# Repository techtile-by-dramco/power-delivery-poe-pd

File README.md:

# Power delivery board 

This powered device (PD) board is made for the Techtile infrastructure and separates the voltage from the data coming from the ethernet CAT6 24AWG cable. It further converts the voltage to a lower usable 5V voltage with a galvanically isolated dc/dc converter (maximum output power 20W). This board is compatible with the IEEE802.3af/at/bt standard. 

To comply with the IEEE 802.3 standard a delay network was added. This prevents excessive startup power that occurs due to the high input capacitors of the DC/DC converters. During INRUSH state, the power may not exceed Power Class 3 (approximately 13W). Otherwise, the PSE may turn off the PD. (See standard and datasheet NCP1096)

Several USBs and connectors are available to power the peripherals on each tile.

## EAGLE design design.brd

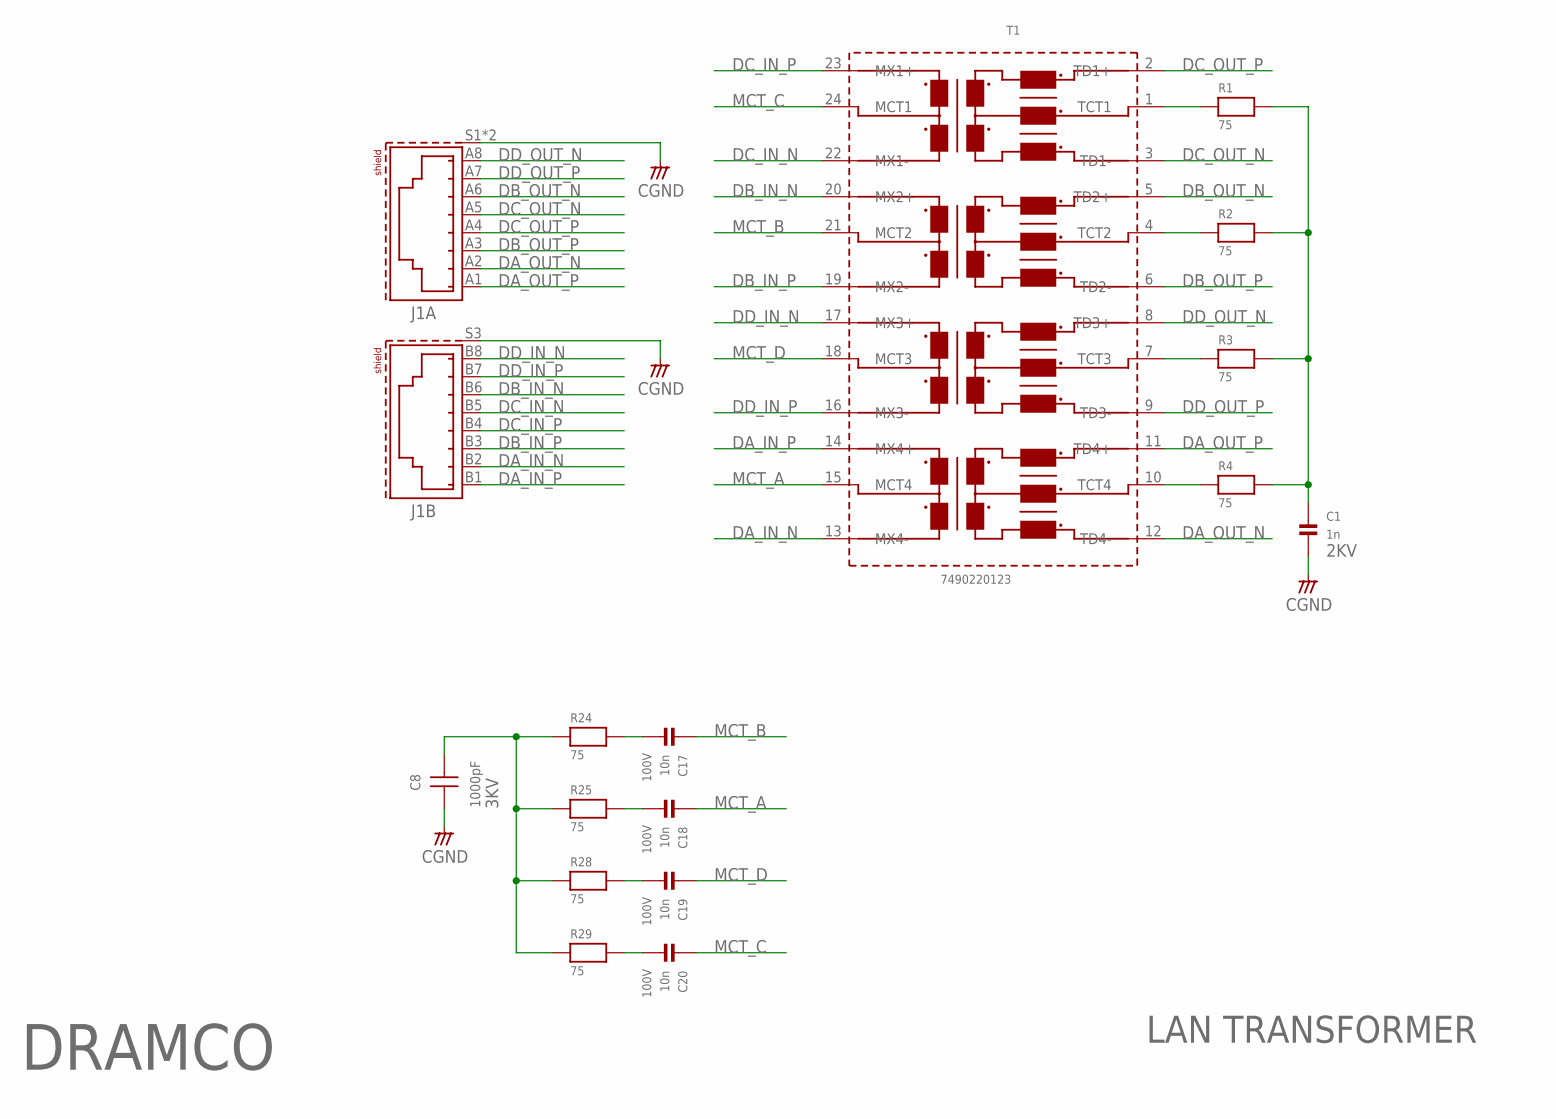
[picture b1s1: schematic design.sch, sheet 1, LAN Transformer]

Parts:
C1: 1n; 1206
C8: 1000pF; WCAP-CSMH_1808_H2.0
C17, C18, C19, C20: 10n; 0603
J1: 615016137621
R1, R2, R3, R4, R24, R25, R28, R29: 75; 0805
T1: 7490220123; 749022012X

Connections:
CGND: C1.2, C8.1, J1.S1 (SHIELD), J1.S2 (SHIELD), J1.S3 (SHIELD)
DA_IN_N: J1.B2 (7), T1.13 (MX4-)
DA_IN_P: J1.B1 (8), T1.14 (MX4+)
DA_OUT_N: J1.A2 (7), T1.12 (TD4-)
DA_OUT_P: J1.A1 (8), T1.11 (TD4+)
DB_IN_N: J1.B6 (3), T1.20 (MX2+)
DB_IN_P: J1.B3 (6), T1.19 (MX2-)
DB_OUT_N: J1.A6 (3), T1.5 (TD2+)
DB_OUT_P: J1.A3 (6), T1.6 (TD2-)
DC_IN_N: J1.B5 (4), T1.22 (MX1-)
DC_IN_P: J1.B4 (5), T1.23 (MX1+)
DC_OUT_N: J1.A5 (4), T1.3 (TD1-)
DC_OUT_P: J1.A4 (5), T1.2 (TD1+)
DD_IN_N: J1.B8 (1), T1.17 (MX3+)
DD_IN_P: J1.B7 (2), T1.16 (MX3-)
DD_OUT_N: J1.A8 (1), T1.8 (TD3+)
DD_OUT_P: J1.A7 (2), T1.9 (TD3-)
MCT_A: C18.1, T1.15 (MCT4); also elsewhere on the board
MCT_B: C17.1, T1.21 (MCT2); also elsewhere on the board
MCT_C: C20.1, T1.24 (MCT1); also elsewhere on the board
MCT_D: C19.1, T1.18 (MCT3); also elsewhere on the board
unnamed: R4.1, T1.10 (TCT4)
unnamed: R3.1, T1.7 (TCT3)
unnamed: R2.1, T1.4 (TCT2)
unnamed: R1.1, T1.1 (TCT1)
unnamed: C1.1, R1.2, R2.2, R3.2, R4.2
unnamed: C8.2, R24.1, R25.1, R28.1, R29.1
unnamed: C17.2, R24.2
unnamed: C18.2, R25.2
unnamed: C19.2, R28.2
unnamed: C20.2, R29.2

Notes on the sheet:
2KV
3KV
100V
LAN TRANSFORMER
DRAMCO

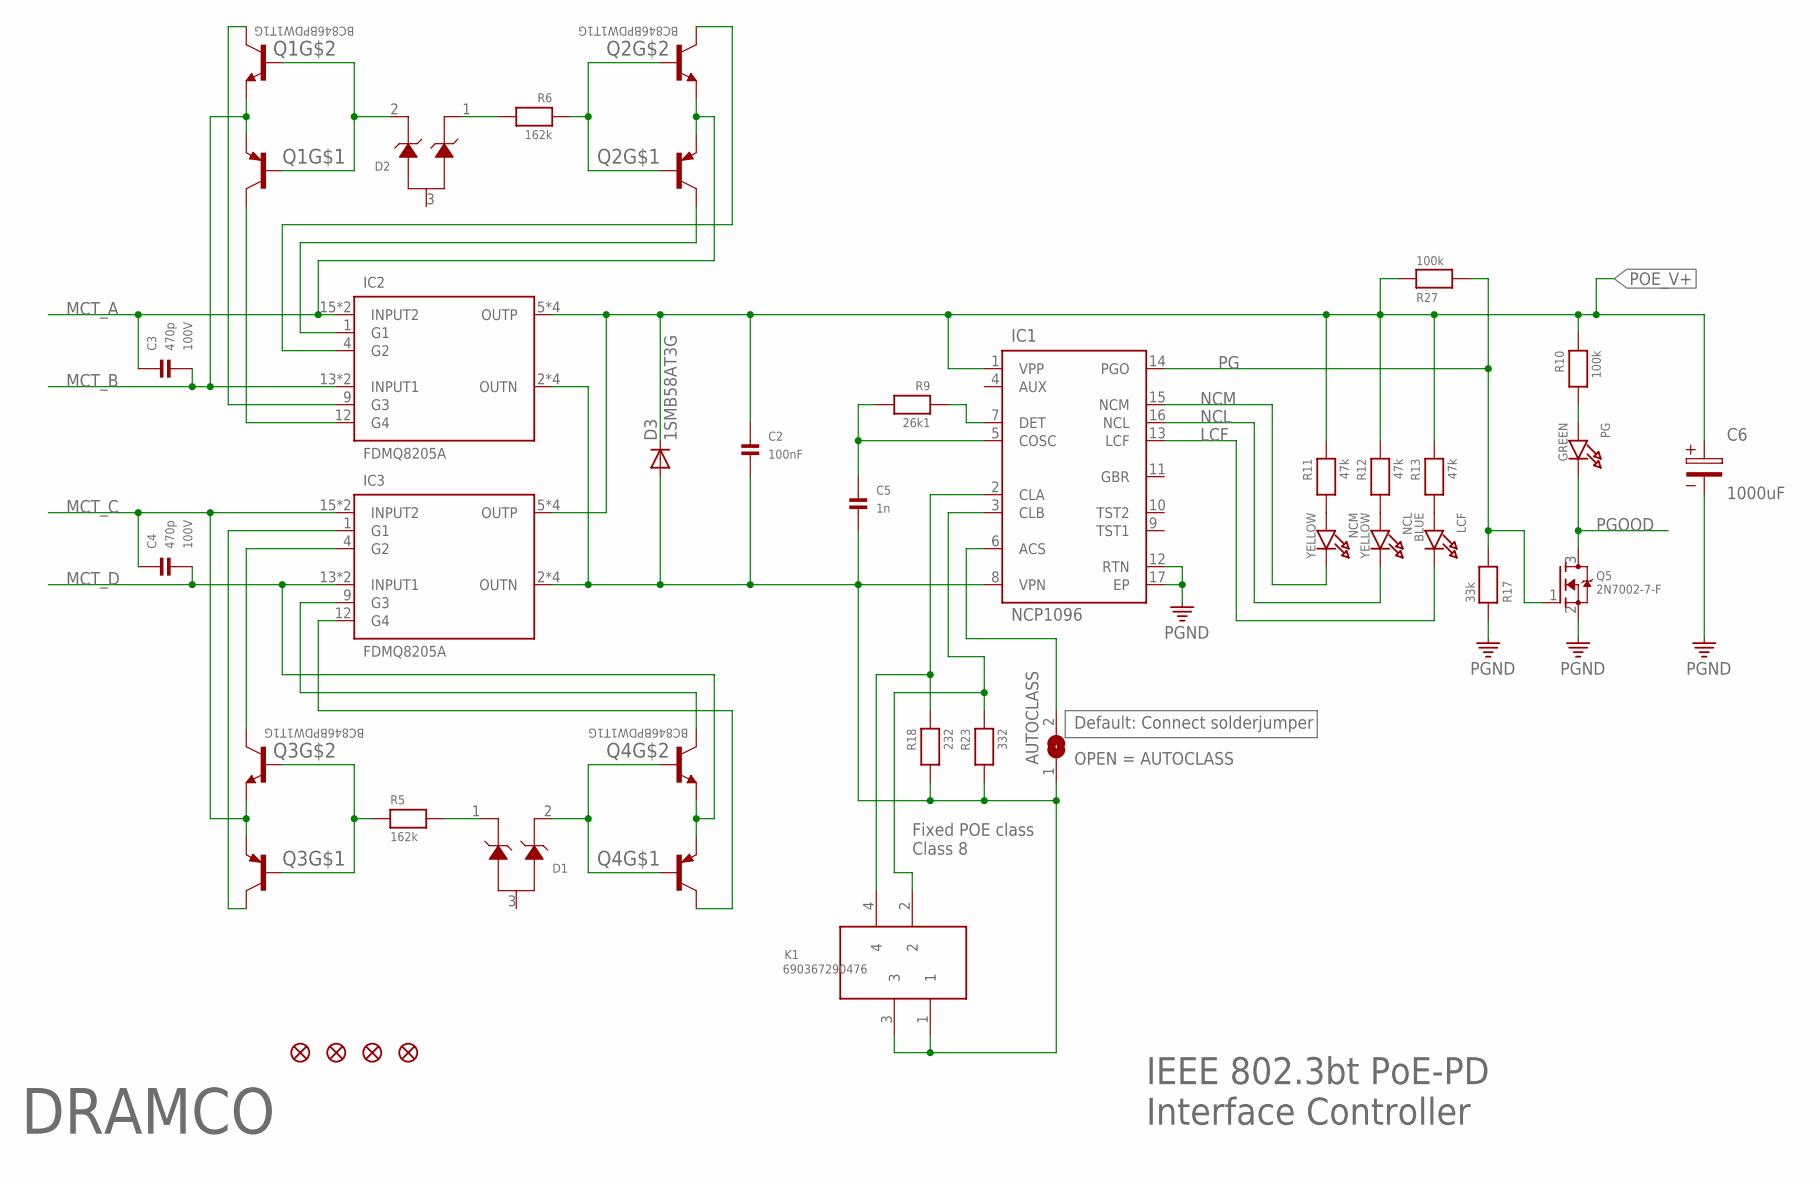
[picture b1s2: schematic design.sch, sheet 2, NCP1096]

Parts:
AUTOCLASS: SOLDERJUMPERREFLOW; SOLDERJUMPER_REFLOW
C2: 100nF; 0805
C3, C4: 470p; 0603
C5: 1n; 0603
C6: 1000uF; 16X7.5X1.1(DXAXB)
D1, D2: MMBZ27VALT1G; SOT95P237X111-3N
D3: 1SMB58AT3G; DO-214AC
FID1, FID2, FID3, FID5: FIDUCIAL""; FIDUCIAL_1MM
IC1: NCP1096; TSSOP16
IC2, IC3: FDMQ8205A; WDFN-12
K1: 690367290476
LCF: BLUE; CHIPLED_0805
NCL: YELLOW; CHIPLED_0805
NCM: YELLOW; CHIPLED_0805
PG: GREEN; CHIPLED_0805
Q1, Q2, Q3, Q4: BC846BPDW1T1G; SOT65P210X110-6N
Q5: 2N7002-7-F; SOT23-WIDE
R5, R6: 162k; 0603
R9: 26k1; 0603
R10, R27: 100k; 0603
R11, R12, R13: 47k; 0603
R17: 33k; 0603
R18: 232; 0603
R23: 332; 0603

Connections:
LCF: IC1.13 (LCF), LCF.C
MCT_A: C3.1, IC2.15 (INPUT2), IC2.16 (INPUT2), Q2.1 (E2), Q2.4 (E1); also elsewhere on the board
MCT_B: C3.2, IC2.13 (INPUT1), IC2.14 (INPUT1), Q1.1 (E2), Q1.4 (E1); also elsewhere on the board
MCT_C: C4.1, IC3.15 (INPUT2), IC3.16 (INPUT2), Q3.1 (E2), Q3.4 (E1); also elsewhere on the board
MCT_D: C4.2, IC3.13 (INPUT1), IC3.14 (INPUT1), Q4.1 (E2), Q4.4 (E1); also elsewhere on the board
unnamed: IC1.2 (CLA), K1.4, R18.1
unnamed: NCM.A, R11.2
unnamed: IC1.7 (DET), R9.1
unnamed: C5.1, IC1.5 (COSC), R9.2
unnamed: PG.A, R10.2
unnamed: Q3.2 (B2), Q3.5 (B1), R5.1
unnamed: NCL.A, R12.2
unnamed: D1.2, Q4.2 (B2), Q4.5 (B1)
unnamed: IC3.4 (G2), Q3.6 (C2)
unnamed: IC3.1 (G1), Q3.3 (C1)
unnamed: LCF.A, R13.2
unnamed: IC3.12 (G4), Q4.3 (C1)
unnamed: IC3.9 (G3), Q4.6 (C2)
unnamed: Q2.2 (B2), Q2.5 (B1), R6.1
unnamed: IC1.3 (CLB), K1.2, R23.1
unnamed: D1.1, R5.2
unnamed: AUTOCLASS.2, IC1.6 (ACS)
unnamed: D2.2, Q1.2 (B2), Q1.5 (B1)
unnamed: IC2.4 (G2), Q2.6 (C2)
unnamed: IC2.1 (G1), Q2.3 (C1)
unnamed: IC2.12 (G4), Q1.3 (C1)
unnamed: D2.1, R6.2
unnamed: IC2.9 (G3), Q1.6 (C2)
NCL: IC1.16 (NCL), NCL.C
NCM: IC1.15 (NCM), NCM.C
PG: IC1.14 (PGO), Q5.1 (G), R17.2, R27.2; also elsewhere on the board
PGND: C6.2, IC1.12 (RTN), IC1.17 (EP), Q5.2 (S), R17.1; also elsewhere on the board
PGOOD: PG.C, Q5.3 (D); also elsewhere on the board
POE_V+: C2.1, C6.1, D3.C, IC1.1 (VPP), IC2.5 (OUTP), IC2.6 (OUTP), IC2.7 (OUTP), IC2.8 (OUTP), IC3.5 (OUTP), IC3.6 (OUTP), IC3.7 (OUTP), IC3.8 (OUTP), R10.1, R11.1, R12.1, R13.1, R27.1; also elsewhere on the board
VPN: AUTOCLASS.1, C2.2, C5.2, D3.A, IC1.8 (VPN), IC2.2 (OUTN), IC2.3 (OUTN), IC2.10 (OUTN), IC2.11 (OUTN), IC3.2 (OUTN), IC3.3 (OUTN), IC3.10 (OUTN), IC3.11 (OUTN), K1.1, K1.3, R18.2, R23.2

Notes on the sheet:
100V
IEEE 802.3bt PoE-PD Interface Controller
DRAMCO
Fixed POE class Class 8
OPEN = AUTOCLASS
Default: Connect solderjumper

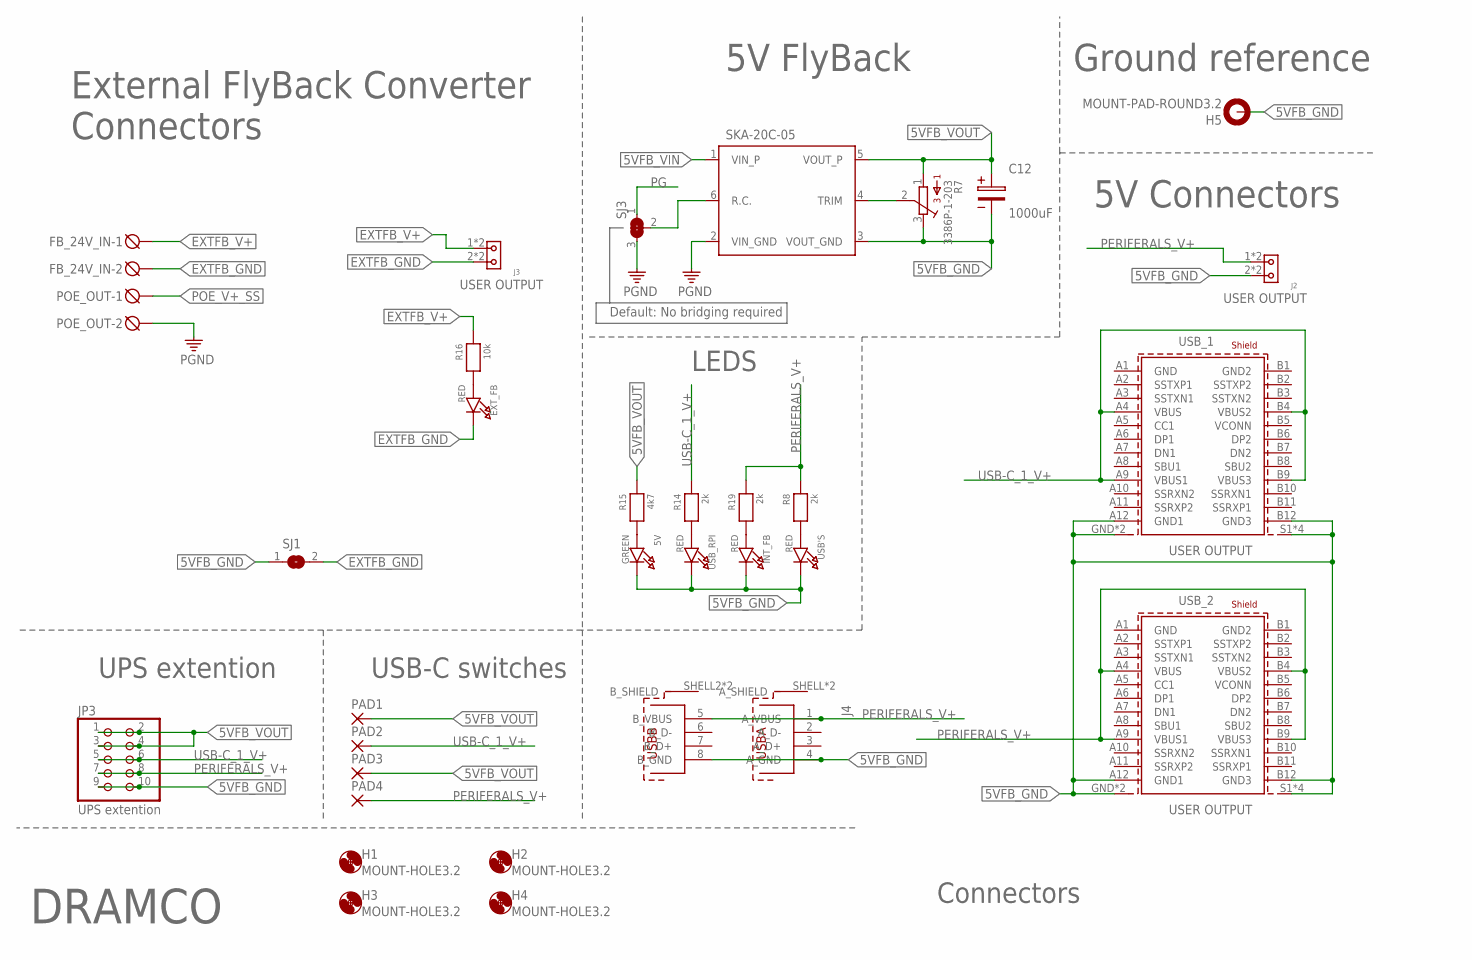
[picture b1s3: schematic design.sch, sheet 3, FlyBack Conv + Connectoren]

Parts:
5V: GREEN; CHIPLED_0805
C12: 1000uF; 10X5X0.9(DXAXB)
EXT_FB: RED; CHIPLED_0805
FB_24V_IN: DG3XX-02-5.0; DG306-5.0-02P
H1, H2, H3, H4: MOUNT-HOLE3.2; 3,2
H5: MOUNT-PAD-ROUND3.2; 3,2-PAD
INT_FB: RED; CHIPLED_0805
J2, J3: 691411510002
J4: 61400826021
JP3: UPS extention; 2X05
PAD1, PAD2, PAD3, PAD4: SMD5; SMD2,54-5,08
POE_OUT: DG3XX-02-5.0; DG306-5.0-02P
R7: 3386P-1-203; 3386P
R8, R14, R19: 2k; 0603
R15: 4k7; 0603
R16: 10k; 0603
SJ1: SOLDERJUMPERREFLOW; SOLDERJUMPER_REFLOW
SJ3: SOLDERJUMPER_2WAY; SOLDERJUMPER_2WAY_OPEN_NOPASTE
SKA-20C-05: SKA20C-05; SKA20SERIES
USB'S: RED; CHIPLED_0805
USB_1, USB_2: 632723100011
USB_RPI: RED; CHIPLED_0805

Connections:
5VFB_GND: 5V.C, C12.2, H5.B3,2, INT_FB.C, J2.2, J2.A2 (2), J4.4 (A_GND), J4.8 (B_GND), JP3.9, JP3.10, R7.3, SJ1.1, SKA-20C-05.3 (VOUT_GND), USB'S.C, USB_1.A12 (GND1), USB_1.B12 (GND3), USB_1.GND (SHIELD), USB_1.GND1 (SHIELD), USB_1.S1 (SHIELD1), USB_1.S2 (SHIELD1), USB_1.S3 (SHIELD1), USB_1.S4 (SHIELD1), USB_2.A12 (GND1), USB_2.B12 (GND3), USB_2.GND (SHIELD), USB_2.GND1 (SHIELD), USB_2.S1 (SHIELD1), USB_2.S2 (SHIELD1), USB_2.S3 (SHIELD1), USB_2.S4 (SHIELD1), USB_RPI.C
5VFB_VIN: SKA-20C-05.1 (VIN_P); also elsewhere on the board
5VFB_VOUT: C12.1, JP3.1, JP3.2, JP3.3, JP3.4, PAD1.1, PAD3.1, R7.1, R15.1, SKA-20C-05.5 (VOUT_P)
EXTFB_GND: EXT_FB.C, FB_24V_IN.2, J3.2, J3.A2 (2), SJ1.2
EXTFB_V+: FB_24V_IN.1, J3.1, J3.A1 (1), R16.1
unnamed: INT_FB.A, R19.2
unnamed: R8.2, USB'S.A
unnamed: R14.2, USB_RPI.A
unnamed: 5V.A, R15.2
unnamed: EXT_FB.A, R16.2
unnamed: R7.2, SKA-20C-05.4 (TRIM)
unnamed: SJ3.2, SKA-20C-05.6 (R.C.)
PERIFERALS_V+: J2.1, J2.A1 (1), J4.1 (A_VBUS), J4.5 (B_VBUS), JP3.7, JP3.8, PAD4.1, R8.1, R19.1, USB_2.A4 (VBUS), USB_2.A9 (VBUS1), USB_2.B4 (VBUS2), USB_2.B9 (VBUS3)
PG: SJ3.1; also elsewhere on the board
PGND: POE_OUT.2, SJ3.3, SKA-20C-05.2 (VIN_GND); also elsewhere on the board
POE_V+_SS: POE_OUT.1; also elsewhere on the board
USB-C_1_V+: JP3.5, JP3.6, PAD2.1, R14.1, USB_1.A4 (VBUS), USB_1.A9 (VBUS1), USB_1.B4 (VBUS2), USB_1.B9 (VBUS3)

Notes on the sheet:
Connectors
DRAMCO
5V Connectors
5V FlyBack
USB-C switches
External FlyBack Converter Connectors
USER OUTPUT
Ground reference
LEDS
UPS extention
Default: No bridging required

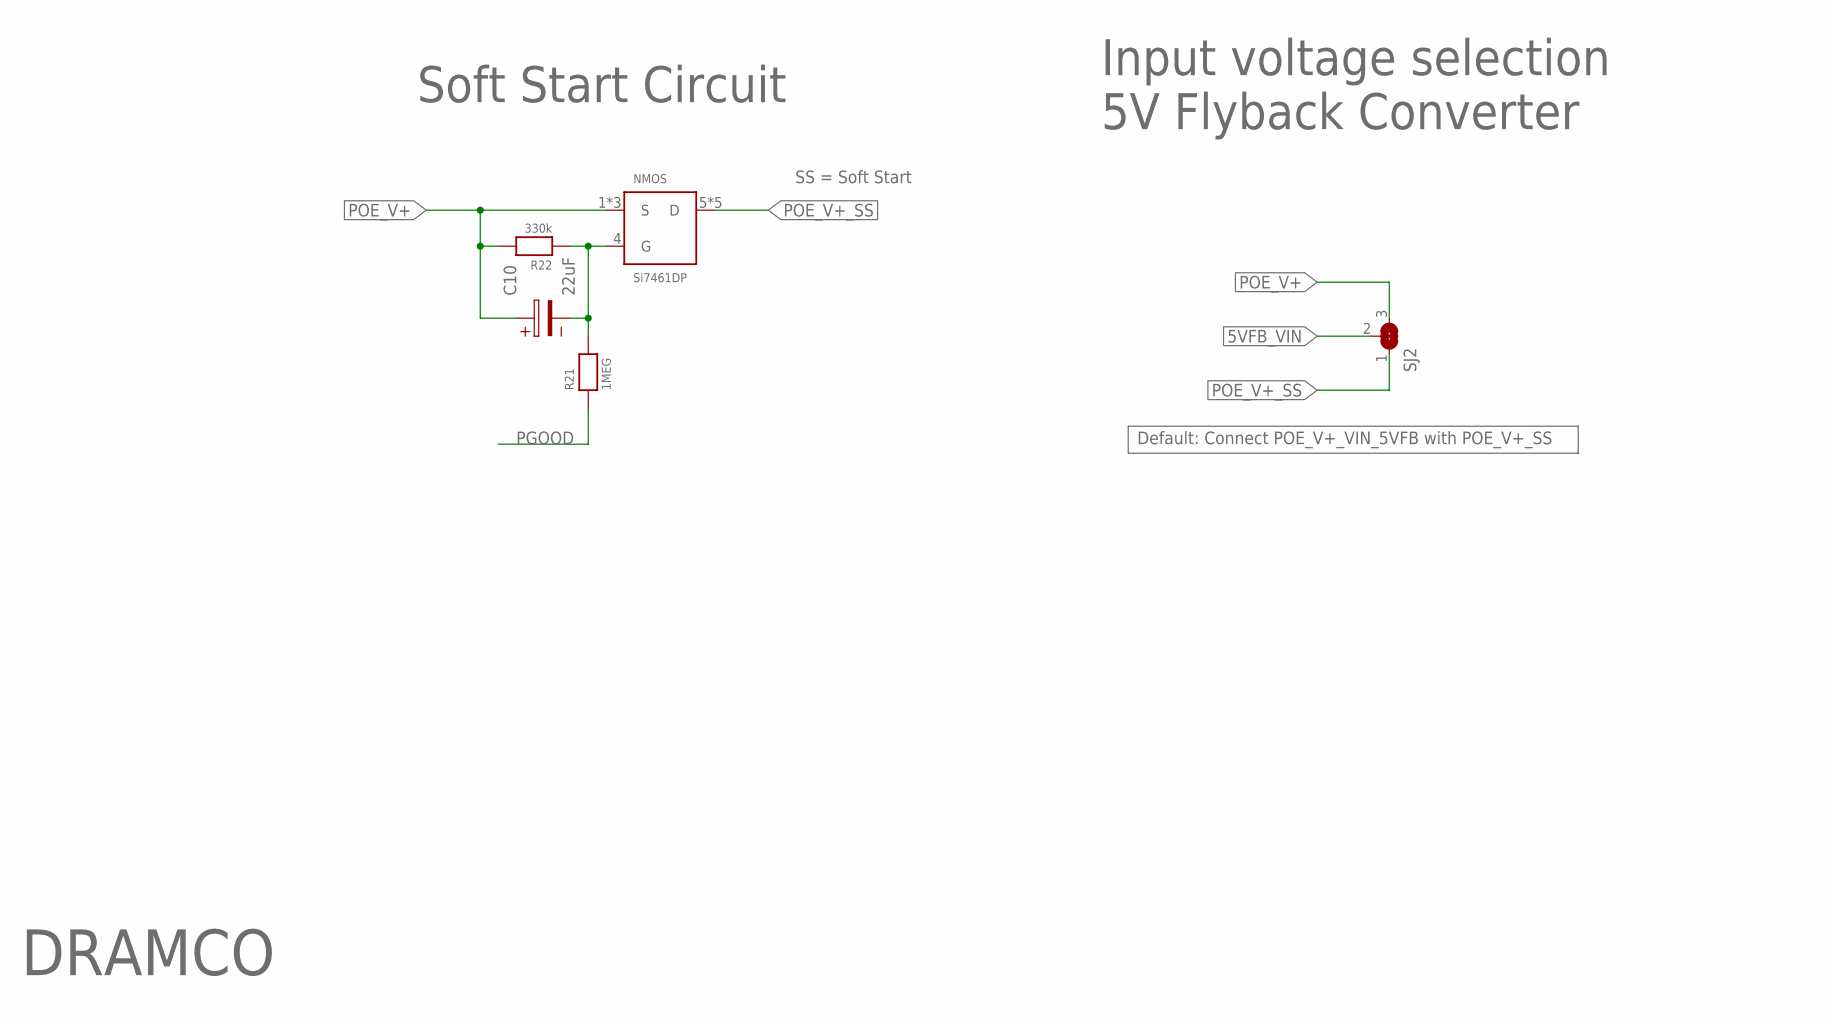
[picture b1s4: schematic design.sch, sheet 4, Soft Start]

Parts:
C10: 22uF; 5X2X0.8(DXAXB)
NMOS: Si7461DP; SO-8
R21: 1MEG; 0603
R22: 330k; 0603
SJ2: SOLDERJUMPER_2WAY; SOLDERJUMPER_2WAY_OPEN_NOPASTE

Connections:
5VFB_VIN: SJ2.2; also elsewhere on the board
unnamed: C10.2, NMOS.4 (G), R21.2, R22.1
PGOOD: R21.1; also elsewhere on the board
POE_V+: C10.1, NMOS.1 (S), NMOS.2 (S), NMOS.3 (S), R22.2, SJ2.3; also elsewhere on the board
POE_V+_SS: NMOS.5 (D), NMOS.6 (D), NMOS.7 (D), NMOS.8 (D), NMOS.9 (D), SJ2.1; also elsewhere on the board

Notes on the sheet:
DRAMCO
Default: Connect POE_V+_VIN_5VFB with POE_V+_SS
SS = Soft Start
Input voltage selection 5V Flyback Converter
Soft Start Circuit

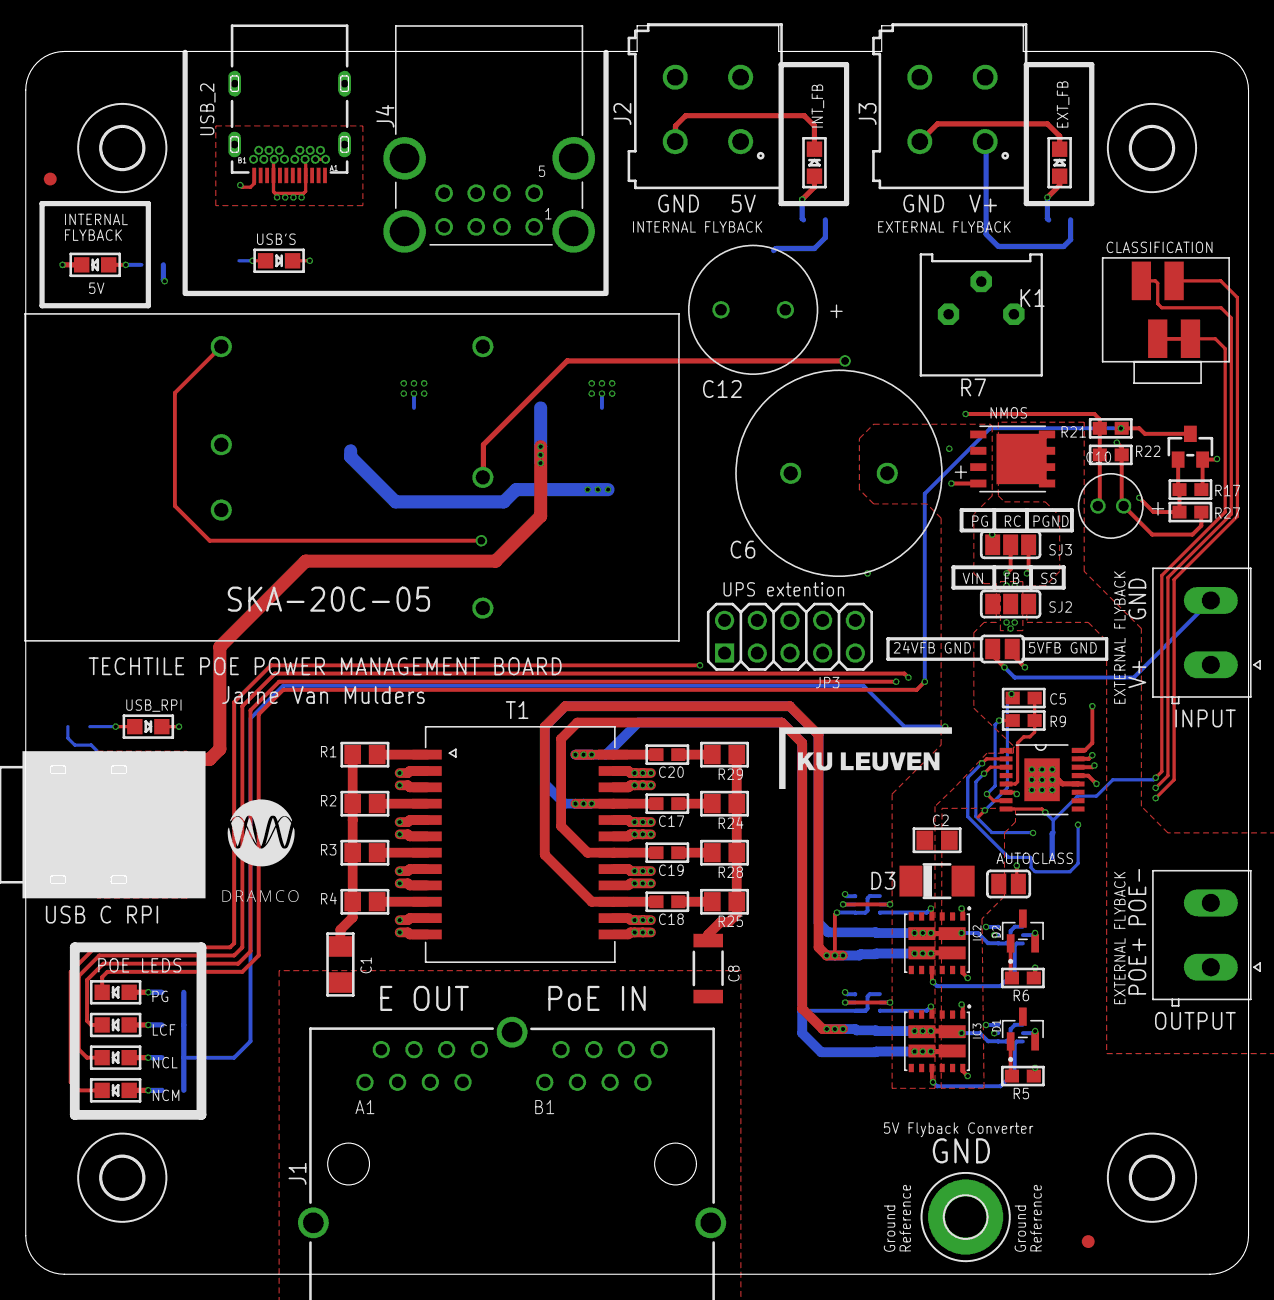
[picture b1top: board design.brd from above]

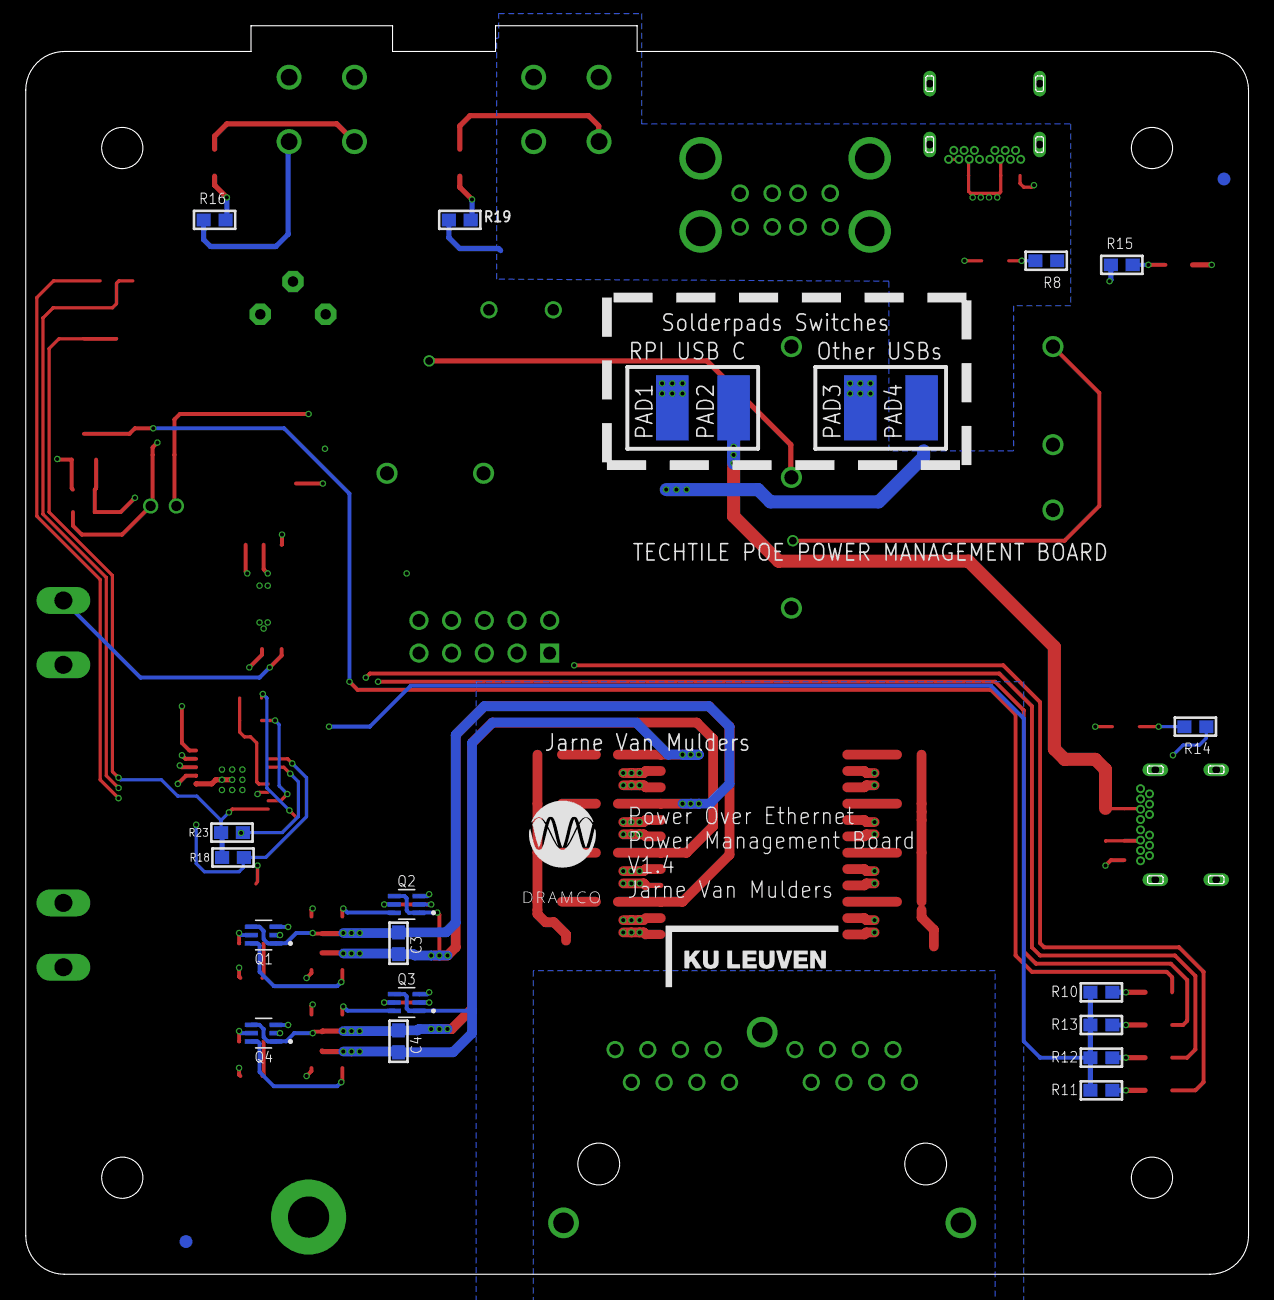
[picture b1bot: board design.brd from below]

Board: 4 copper layers, 95.0 x 97.0 mm, 90 parts (23 on the bottom side), 78 nets.

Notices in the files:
parts and their libraries:
microbuilder: This work is placed in the public domain, and may be freely used for commercial and non-commercial work with the following conditions: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
o166547v244 Eagle_WR-TBL Spring Clamp: Copyright: Würth Elektronik
supply0: Copyright (C) 2007, Bob Starr
